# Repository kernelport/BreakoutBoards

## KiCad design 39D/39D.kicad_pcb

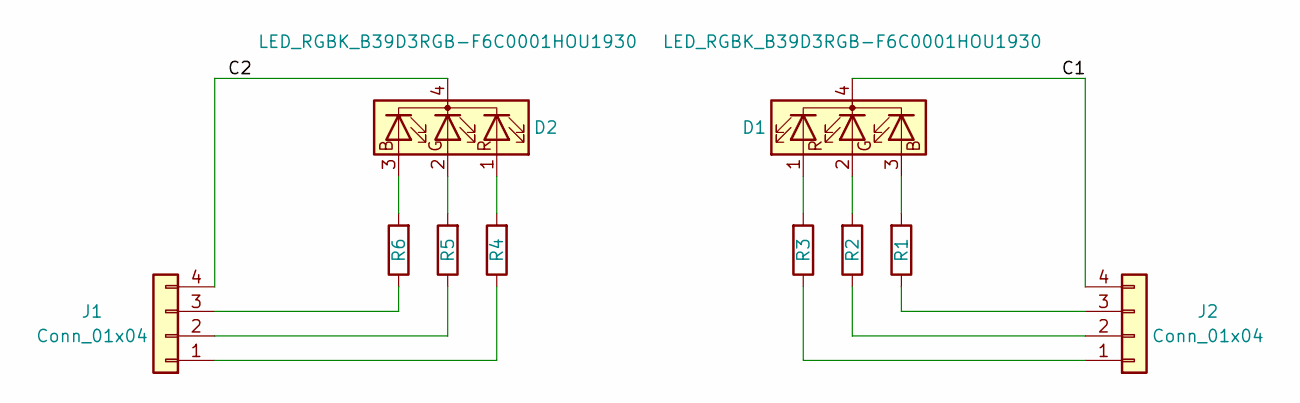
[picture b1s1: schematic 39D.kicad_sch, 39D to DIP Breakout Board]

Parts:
D1, D2: LED_RGBK_B39D3RGB-F6C0001HOU1930; B39D3RGB-F6C0001HOU1930_HVK-mini; Digikey 3147-B39D3RGB-F6C0001HOU1930CT-ND
J1, J2: Conn_01x04; PinHeader_1x04_P2.54mm_Vertical
R1, R2, R3, R4, R5, R6: R; R_0603_1608Metric

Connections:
/C1: D1.4 (K), J2.4
/C2: D2.4 (K), J1.4
unnamed: D1.3 (BA), R1.2
unnamed: D1.2 (GA), R2.2
unnamed: D1.1 (RA), R3.2
unnamed: D2.3 (BA), R6.2
unnamed: D2.2 (GA), R5.2
unnamed: D2.1 (RA), R4.2
unnamed: J1.1, R4.1
unnamed: J1.2, R5.1
unnamed: J1.3, R6.1
unnamed: J2.1, R3.1
unnamed: J2.2, R2.1
unnamed: J2.3, R1.1

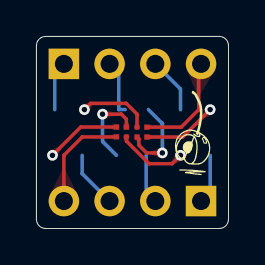
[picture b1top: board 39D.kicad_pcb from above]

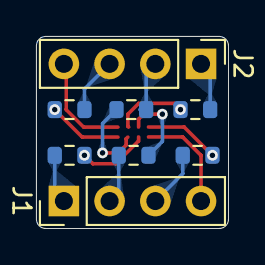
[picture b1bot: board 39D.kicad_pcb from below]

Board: 2 copper layers, 10.7 x 10.7 mm, 10 parts (8 on the bottom side), 14 nets.

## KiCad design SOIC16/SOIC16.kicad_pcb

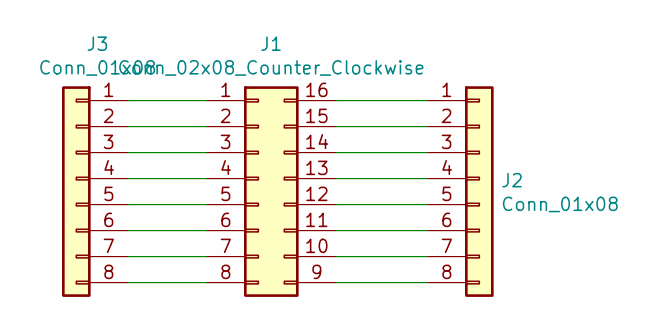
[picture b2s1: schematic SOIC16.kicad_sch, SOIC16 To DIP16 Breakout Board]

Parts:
J1: Conn_02x08_Counter_Clockwise; SOIC-16_3.9x9.9mm_P1.27mm
J2, J3: Conn_01x08; PinHeader_1x08_P2.54mm_Vertical

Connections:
unnamed: J1.1, J3.1
unnamed: J1.2, J3.2
unnamed: J1.3, J3.3
unnamed: J1.4, J3.4
unnamed: J1.5, J3.5
unnamed: J1.6, J3.6
unnamed: J1.7, J3.7
unnamed: J1.8, J3.8
unnamed: J1.9, J2.8
unnamed: J1.10, J2.7
unnamed: J1.11, J2.6
unnamed: J1.12, J2.5
unnamed: J1.13, J2.4
unnamed: J1.14, J2.3
unnamed: J1.15, J2.2
unnamed: J1.16, J2.1

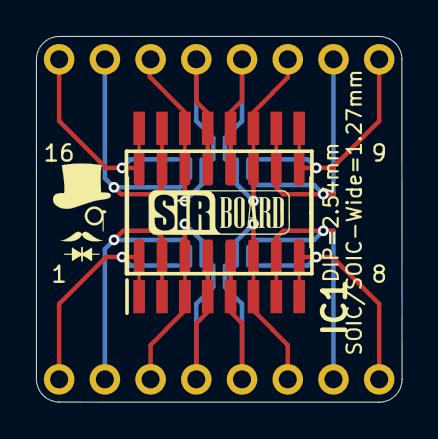
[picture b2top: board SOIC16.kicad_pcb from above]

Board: 2 copper layers, 20.3 x 20.3 mm, 4 parts (0 on the bottom side), 16 nets.

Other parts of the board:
IC1: SI8622ED-B-ISR 5kV; SOIC127P1030X265-16N

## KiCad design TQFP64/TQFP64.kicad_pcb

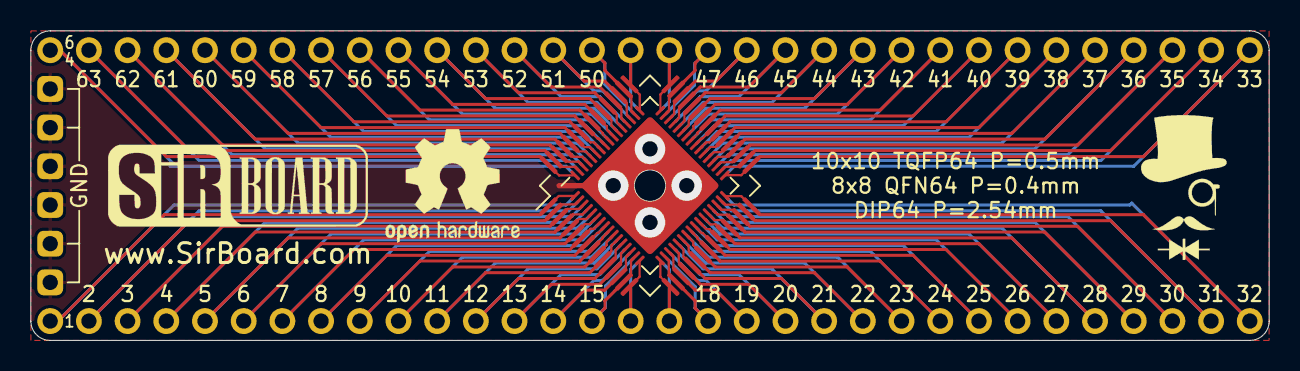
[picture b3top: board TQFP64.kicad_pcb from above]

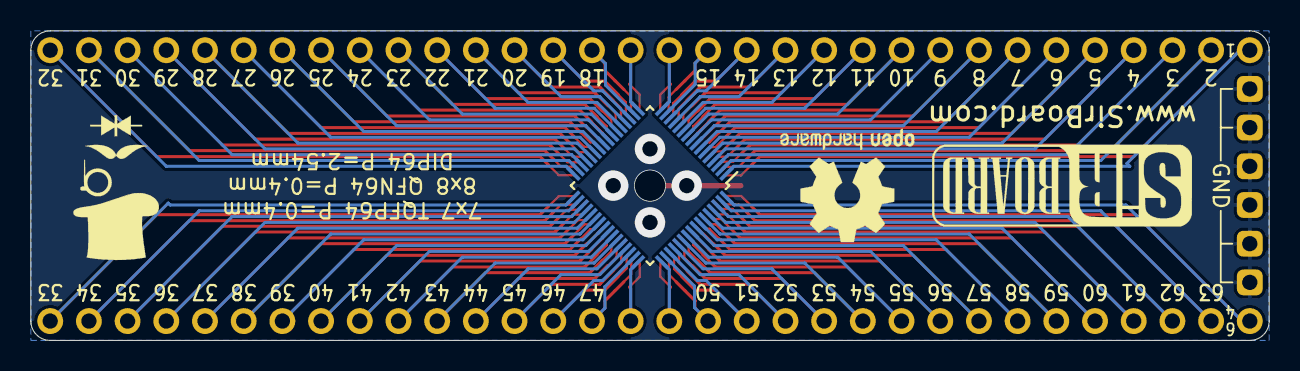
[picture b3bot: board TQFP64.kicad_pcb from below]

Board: 2 copper layers, 81.3 x 20.3 mm, 6 parts (4 on the bottom side), 65 nets.

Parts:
J1, J5: Conn_01x32; PinHeader_1x32_P2.54mm_Vertical
J2: Conn_02x32_Counter_Clockwise; TQFP-64_10x10mm_P0.5mm
J3: Conn_02x32_Counter_Clockwise; QFN-64-1EP_8x8mm_P0.4mm_EP6.5x6.5mm
J4: Conn_02x32_Counter_Clockwise; TQFP-64_7x7mm_P0.4mm
J6: Conn_01x06; PinHeader_1x06_P2.54mm_Vertical

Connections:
unnamed: J1.1, J2.1, J3.1, J4.64
unnamed: J1.2, J2.2, J3.2, J4.63
unnamed: J1.3, J2.3, J3.3, J4.62
unnamed: J1.4, J2.4, J3.4, J4.61
unnamed: J1.5, J2.5, J3.5, J4.60
unnamed: J1.6, J2.6, J3.6, J4.59
unnamed: J1.7, J2.7, J3.7, J4.58
unnamed: J1.8, J2.8, J3.8, J4.57
unnamed: J1.9, J2.9, J3.9, J4.56
unnamed: J1.10, J2.10, J3.10, J4.55
unnamed: J1.11, J2.11, J3.11, J4.54
unnamed: J1.12, J2.12, J3.12, J4.53
unnamed: J1.13, J2.13, J3.13, J4.52
unnamed: J1.14, J2.14, J3.14, J4.51
unnamed: J1.15, J2.15, J3.15, J4.50
unnamed: J1.16, J2.16, J3.16, J4.49
unnamed: J1.17, J2.17, J3.17, J4.48
unnamed: J1.18, J2.18, J3.18, J4.47
unnamed: J1.19, J2.19, J3.19, J4.46
unnamed: J1.20, J2.20, J3.20, J4.45
unnamed: J1.21, J2.21, J3.21, J4.44
unnamed: J1.22, J2.22, J3.22, J4.43
unnamed: J1.23, J2.23, J3.23, J4.42
unnamed: J1.24, J2.24, J3.24, J4.41
unnamed: J1.25, J2.25, J3.25, J4.40
unnamed: J1.26, J2.26, J3.26, J4.39
unnamed: J1.27, J2.27, J3.27, J4.38
unnamed: J1.28, J2.28, J3.28, J4.37
unnamed: J1.29, J2.29, J3.29, J4.36
unnamed: J1.30, J2.30, J3.30, J4.35
unnamed: J1.31, J2.31, J3.31, J4.34
unnamed: J1.32, J2.32, J3.32, J4.33
unnamed: J2.33, J3.33, J4.32, J5.32
unnamed: J2.34, J3.34, J4.31, J5.31
unnamed: J2.35, J3.35, J4.30, J5.30
unnamed: J2.36, J3.36, J4.29, J5.29
unnamed: J2.37, J3.37, J4.28, J5.28
unnamed: J2.38, J3.38, J4.27, J5.27
unnamed: J2.39, J3.39, J4.26, J5.26
unnamed: J2.40, J3.40, J4.25, J5.25
unnamed: J2.41, J3.41, J4.24, J5.24
unnamed: J2.42, J3.42, J4.23, J5.23
unnamed: J2.43, J3.43, J4.22, J5.22
unnamed: J2.44, J3.44, J4.21, J5.21
unnamed: J2.45, J3.45, J4.20, J5.20
unnamed: J2.46, J3.46, J4.19, J5.19
unnamed: J2.47, J3.47, J4.18, J5.18
unnamed: J2.48, J3.48, J4.17, J5.17
unnamed: J2.49, J3.49, J4.16, J5.16
unnamed: J2.50, J3.50, J4.15, J5.15
unnamed: J2.51, J3.51, J4.14, J5.14
unnamed: J2.52, J3.52, J4.13, J5.13
unnamed: J2.53, J3.53, J4.12, J5.12
unnamed: J2.54, J3.54, J4.11, J5.11
unnamed: J2.55, J3.55, J4.10, J5.10
unnamed: J2.56, J3.56, J4.9, J5.9
unnamed: J2.57, J3.57, J4.8, J5.8
unnamed: J2.58, J3.58, J4.7, J5.7
unnamed: J2.59, J3.59, J4.6, J5.6
unnamed: J2.60, J3.60, J4.5, J5.5
unnamed: J2.61, J3.61, J4.4, J5.4
unnamed: J2.62, J3.62, J4.3, J5.3
unnamed: J2.63, J3.63, J4.2, J5.2
unnamed: J2.64, J3.64, J4.1, J5.1
unnamed: J3.65, J6.1, J6.2, J6.3, J6.4, J6.5, J6.6

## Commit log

2024-02-16 convert SOIC16 to kicad 7
2024-02-16 add SOIC-Wide-16
2024-03-04 use gitignore global
2024-03-04 add RGB LED Frootprint Adapter 39D
2024-03-04 apdate all footprints an run drc
